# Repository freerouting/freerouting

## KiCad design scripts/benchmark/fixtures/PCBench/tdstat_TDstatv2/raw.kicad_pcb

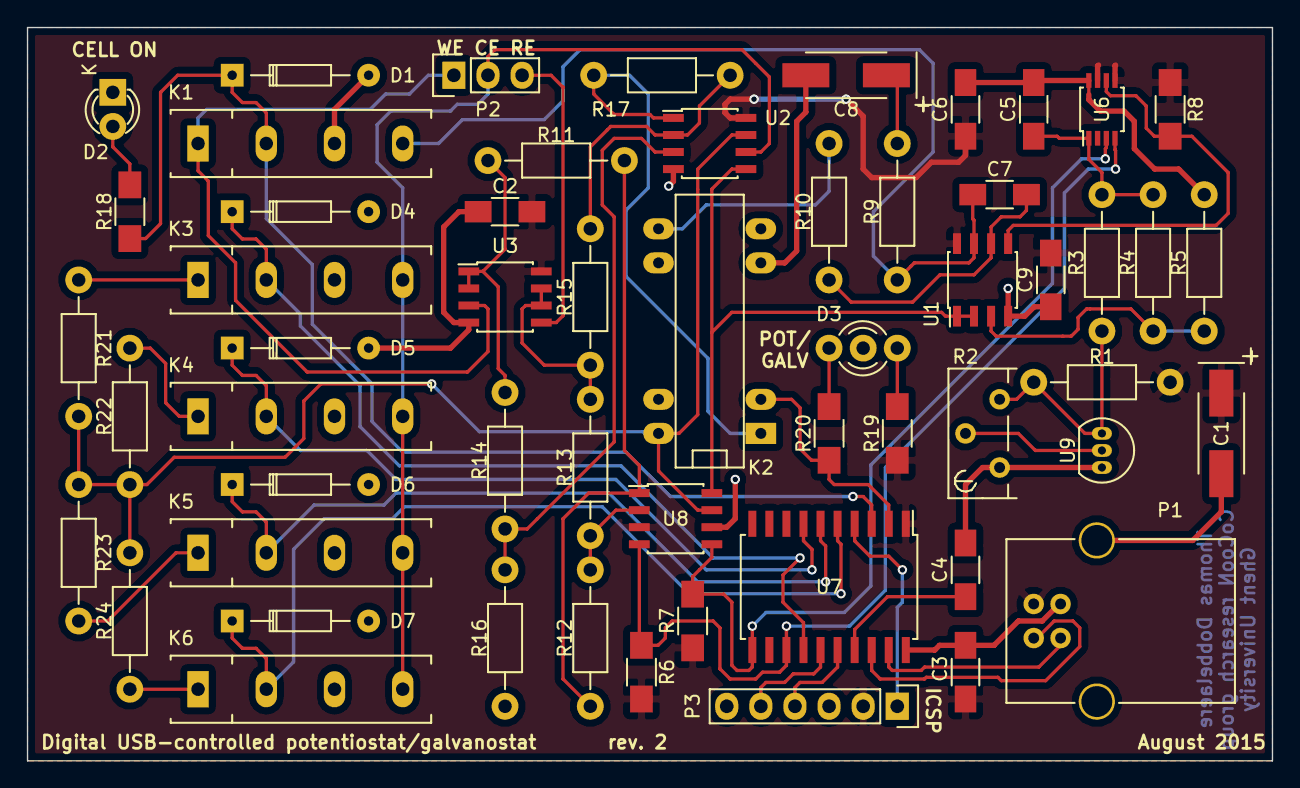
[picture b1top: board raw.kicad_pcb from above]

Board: 2 copper layers, 92.7 x 54.6 mm, 56 parts (0 on the bottom side), 44 nets.

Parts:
C1, C8: 10 µF; TantalC_SizeC_EIA-6032_HandSoldering
C2, C3, C4, C5, C6, C7, C9: 0.1 µF; C_1206_HandSoldering
D1, D4, D5, D6, D7: 1N4148; Diode_DO-35_SOD27_Horizontal_RM10
D2: CELL ON LED; LED-3MM
D3: MODE LED; DUO-LED-3mm
K1, K3, K4, K5, K6: 9007-05-00; RELAY-9007
K2: HE721C0510; RELAY-HE700
P1: USB_B
P2: CELL_CONN; Pin_Header_Straight_1x03
P3: ICSP_CONN; Pin_Header_Straight_1x06
R1: 1k; Resistor_Horizontal_RM10mm
R2: 10k; Potentiometer_Bourns_3296Y_3-8Zoll_Angular_ScrewUp
R3, R23: 10k 0.1%; Resistor_Horizontal_RM10mm
R4: 18k 0.1%; Resistor_Horizontal_RM10mm
R5: 2k 0.1%; Resistor_Horizontal_RM10mm
R6, R7: 4k7; R_1206_HandSoldering
R8: 100k; R_1206_HandSoldering
R9: 27; Resistor_Horizontal_RM10mm
R10: 100k; Resistor_Horizontal_RM10mm
R11, R12, R13, R22: 1k 0.1%; Resistor_Horizontal_RM10mm
R14, R15: 200k 0.1%; Resistor_Horizontal_RM10mm
R16, R17, R24: 100k 0.1%; Resistor_Horizontal_RM10mm
R18, R19, R20: 1k; R_1206_HandSoldering
R21: 100R 0.1%; Resistor_Horizontal_RM10mm
U1, U2, U3: AD8629; SOIC-8_3.9x4.9mm_Pitch1.27mm
U6: MAX5217; TSSOP-8_3x3mm_Pitch0.65mm
U7: PIC16F1459; SOIC-20_7.5x12.8mm_Pitch1.27mm
U8: MCP3422; SOIC-8_3.9x4.9mm_Pitch1.27mm
U9: TL431; TO-92_Inline_Narrow_Oval

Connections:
+5V: C1.1, C2.1, C3.1, C6.1, C9.1, P1.1, P3.2, R1.2, R6.1, R7.1, R8.2, R19.2, U1.8, U2.8, U3.8, U6.5, U6.7, U7.1, U8.3
/CE: K3.4, K4.4, K5.4, K6.4, P2.2, U2.6
/CELL_ON: D1.1, K1.2, R18.2, U7.3
/D+: P1.3, U7.19
/D-: P1.2, U7.18
/GALV_SENSE+: U1.1, U1.2, U2.5, U8.8
/GALV_SENSE-: K2.14, R21.2, R22.2, R23.2, R24.2, U2.7, U8.7
/ICSPCLK: P3.5, U7.15
/ICSPDAT: P3.4, U7.16
/MCLR: P3.1, U7.4
/MODE_SW: K2.2, R20.2, U7.2
/RANGE1: D4.1, K3.2, U7.14
/RANGE2: D5.1, K4.2, U7.7
/RANGE3: D6.1, K5.2, U7.6
/RANGE4: D7.1, K6.2, U7.5
/RE: P2.3, U3.5
/SCL: R7.2, U6.3, U7.11, U8.5
/SDA: R6.2, U6.4, U7.13, U8.4
/V_REF_2.4V: C5.2, R3.2, R4.2, U6.1
/WE: K1.1, P2.1, U3.3
GND: C1.2, C2.2, C3.2, C4.1, C5.1, C6.2, C8.2, C9.2, D1.2, D2.1, D3.2, D4.2, D5.2, D6.2, D7.2, K1.3, K2.6, K3.3, K4.3, K5.3, K6.3, P1.4, P1.5, P3.3, R2.1, R5.1, R16.2, U1.4, U2.4, U3.4, U6.8, U7.20, U8.6, U9.3
unnamed: C4.2, U7.17
unnamed: C7.1, K1.4, R9.1, U1.7
unnamed: C7.2, R10.2, U1.6
unnamed: C8.1, R9.2
unnamed: D2.2, R18.1
unnamed: D3.1, R19.1
unnamed: D3.3, R20.1
unnamed: K2.1, R17.2, U2.1
unnamed: K2.8, R10.1
unnamed: K3.1, R21.1
unnamed: K4.1, R22.1
unnamed: K5.1, R23.1
unnamed: K6.1, R24.1
unnamed: R1.1, R2.3, R3.1, U9.1
unnamed: R2.2, U9.2
unnamed: R4.1, R5.2, U1.3
unnamed: R8.1, U1.5, U6.6
unnamed: R11.1, R12.2, U8.1
unnamed: R11.2, R14.2, U3.1, U3.2
unnamed: R12.1, R13.2, U8.2
unnamed: R13.1, R15.1, U3.6, U3.7
unnamed: R14.1, R16.1, U2.3
unnamed: R15.2, R17.1, U2.2

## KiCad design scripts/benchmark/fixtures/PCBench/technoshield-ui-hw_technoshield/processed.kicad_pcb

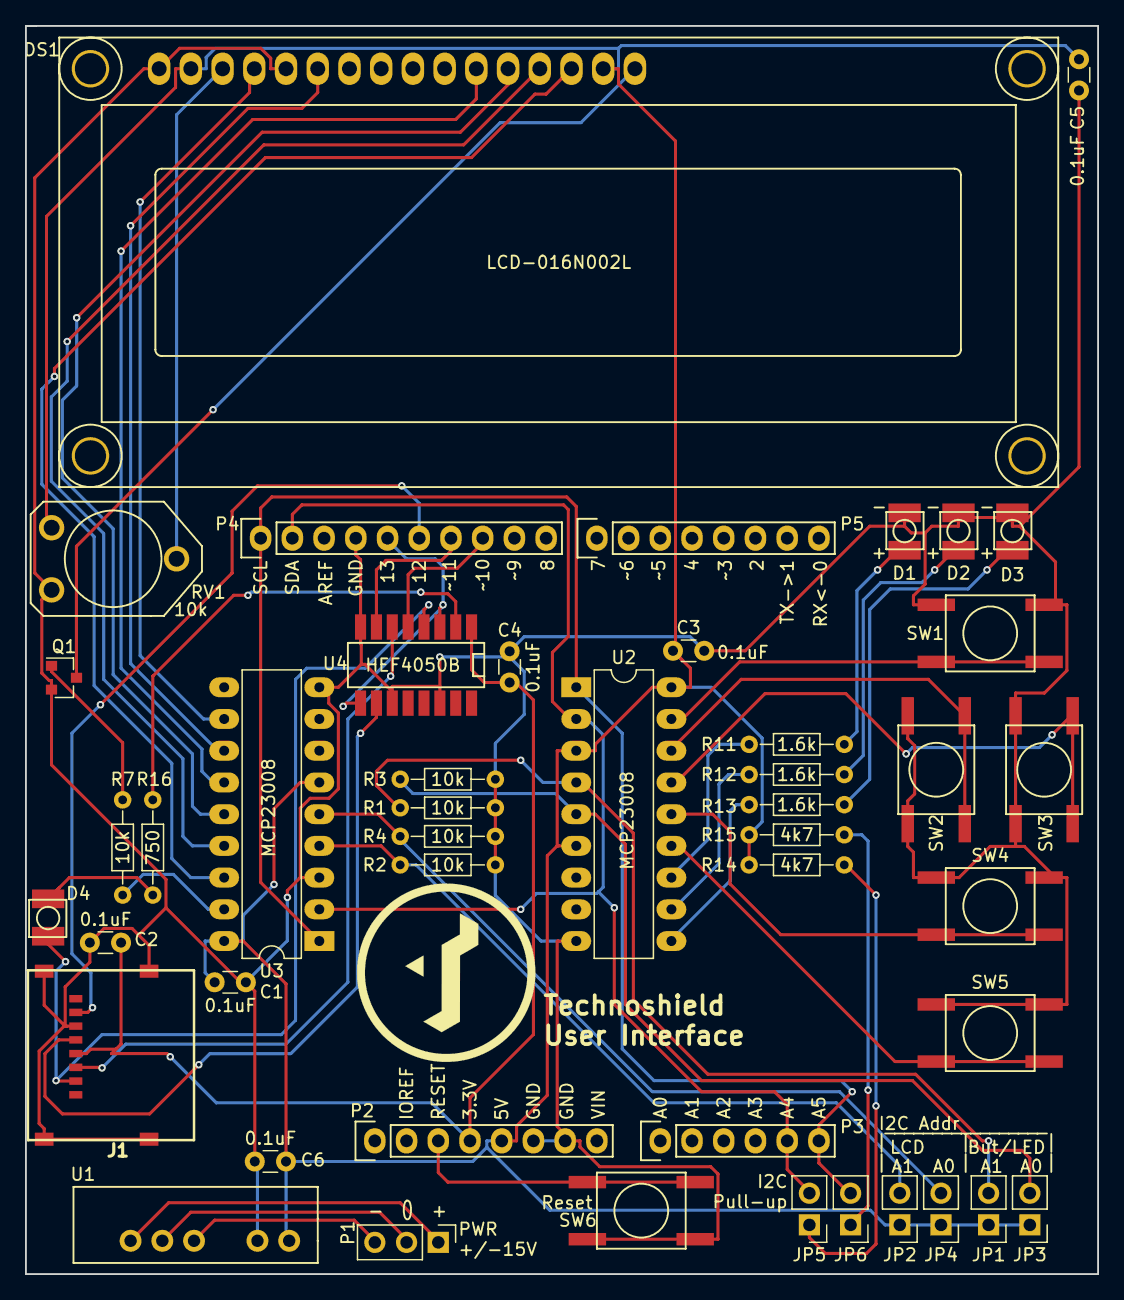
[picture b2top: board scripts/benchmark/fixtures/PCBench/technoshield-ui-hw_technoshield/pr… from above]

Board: 2 copper layers, 85.9 x 99.9 mm, 46 parts (0 on the bottom side), 45 nets.

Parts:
C1, C2, C3, C4, C5, C6: 0.1uF; C_Disc_D3.0mm_W1.6mm_P2.50mm
D1: LS T67K-J1K2-1-Z; T67K
D2: LY T67K-J2L1-26-Z; T67K
D3, D4: LP T67K-E1F2-25-Z; T67K
DS1: LCD-016N002L; WC1602A
J1: 101-00303-68-1-ND; MICRO_SD_HINGE_AMP
JP1, JP2, JP3, JP4, JP5, JP6: JUMPER; Pin_Header_Straight_1x02_Pitch2.54mm
P1: CONN_01X03; Pin_Header_Straight_1x03_Pitch2.54mm
P2: Power; Socket_Strip_Arduino_1x08
P3: Analog; Socket_Strip_Arduino_1x06
P4: Digital; Socket_Strip_Arduino_1x10
P5: Digital; Socket_Strip_Arduino_1x08
Q1: MMBT2222A-7-F; SOT-23
R1, R2, R3, R4, R7: 10k; R_Axial_DIN0204_L3.6mm_D1.6mm_P7.62mm_Horizontal
R11, R12, R13: 1.6k; R_Axial_DIN0204_L3.6mm_D1.6mm_P7.62mm_Horizontal
R14, R15: 4k7; R_Axial_DIN0204_L3.6mm_D1.6mm_P7.62mm_Horizontal
R16: 750; R_Axial_DIN0204_L3.6mm_D1.6mm_P7.62mm_Horizontal
RV1: 10k; POTENTIOMETRE_BOURNS_3319P
SW1, SW2, SW3, SW4, SW5, SW6: SW_PUSH; smt_btn
U1: PDM1-S5-D15-S; PDM1-S
U2, U3: MCP23008; DIP-18_W7.62mm_LongPads
U4: HEF4050B; SO16-3_9mm

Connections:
+3V3: C2.1, C4.1, J1.4, P2.4, U4.1
+5V: C1.1, C3.1, C5.1, C6.1, DS1.2, DS1.15, JP1.1, JP2.1, JP3.1, JP4.1, P2.5, R14.1, R15.1, RV1.1, U1.1, U2.3, U2.6, U2.18, U3.6, U3.18
/10(**/SS): P4.8, U4.5
/11(**/MOSI): P4.7, U4.7
/12(MISO): J1.7, P4.6
/13(SCK): P4.5, U4.3, U4.9
/A4(SDA): JP5.2, P3.5, P4.2, U2.2, U3.2
/A5(SCL): JP6.2, P3.6, P4.1, U2.1, U3.1
/Reset: P2.3, SW6.2
GND: C1.2, C2.2, C3.2, C4.2, C5.2, C6.2, D1.1, D2.1, D3.1, DS1.1, DS1.5, J1.6, J1.SHLD, P2.6, P2.7, P4.4, Q1.2, R1.2, R2.2, R3.2, R4.2, RV1.3, SW1.2, SW2.2, SW3.2, SW4.2, SW5.2, SW6.1, U1.2, U2.9, U3.3, U3.9, U4.8, U4.11, U4.14
unnamed: D1.2, R11.1
unnamed: D2.2, R12.1
unnamed: D3.2, R13.1
unnamed: D4.1, J1.2, U4.4
unnamed: D4.2, R16.1
unnamed: DS1.3, RV1.2
unnamed: DS1.4, U3.11
unnamed: DS1.6, U3.12
unnamed: DS1.11, U3.13
unnamed: DS1.12, U3.14
unnamed: DS1.13, U3.15
unnamed: DS1.14, U3.16
unnamed: DS1.16, Q1.3
unnamed: J1.3, U4.6
unnamed: J1.5, U4.10
unnamed: JP1.2, R1.1, U2.4
unnamed: JP2.2, R2.1, U3.4
unnamed: JP3.2, R3.1, U2.5
unnamed: JP4.2, R4.1, U3.5
unnamed: JP5.1, R14.2
unnamed: JP6.1, R15.2
unnamed: P1.1, U1.6
unnamed: P1.2, U1.5
unnamed: P1.3, U1.4
unnamed: Q1.1, R7.1
unnamed: R7.2, U3.17
unnamed: R11.2, U2.12
unnamed: R12.2, U2.11
unnamed: R13.2, U2.10
unnamed: R16.2, U4.2
unnamed: SW1.1, U2.17
unnamed: SW2.1, U2.16
unnamed: SW3.1, U2.15
unnamed: SW4.1, U2.14
unnamed: SW5.1, U2.13

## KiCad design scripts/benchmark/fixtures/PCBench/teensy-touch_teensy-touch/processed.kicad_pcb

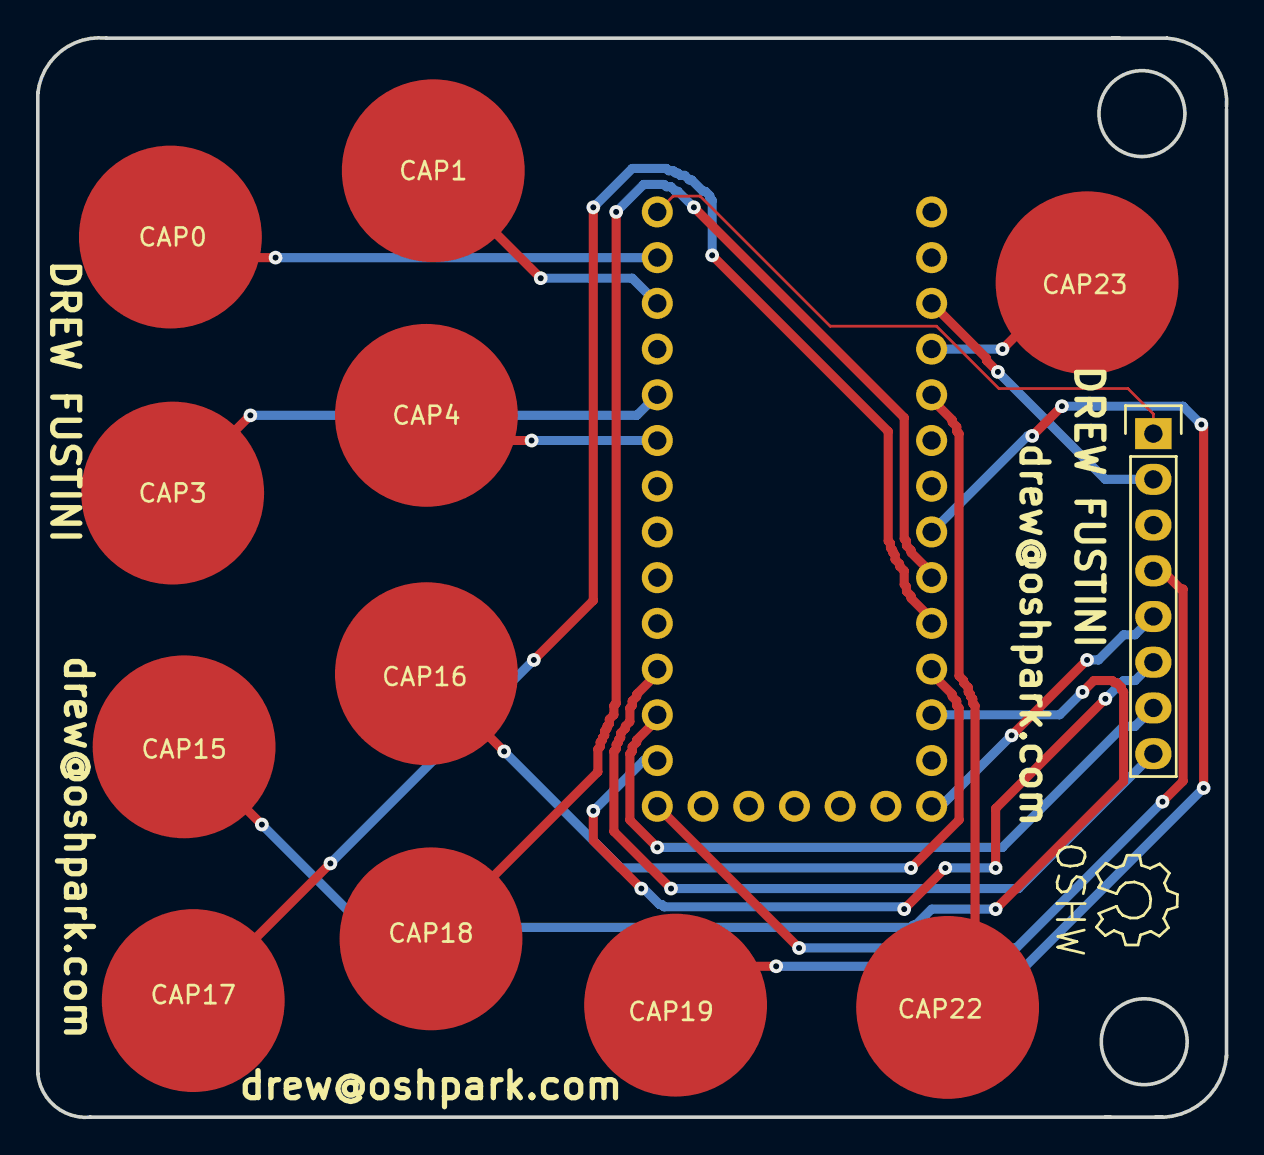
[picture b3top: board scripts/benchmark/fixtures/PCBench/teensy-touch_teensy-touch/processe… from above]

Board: 2 copper layers, 66.0 x 60.0 mm, 13 parts (0 on the bottom side), 18 nets.

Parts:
CAP0, CAP1, CAP3, CAP4, CAP15, CAP16, CAP17, CAP18, CAP19, CAP22, CAP23: CAPSENSE_CIRCLE; CAPSENSE_CIRCLE_D10
J1: TEENSY-LC
J2: OLED_128x64; Pin_Header_Straight_1x08

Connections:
/CAP15: CAP15.1, J1.15
/CAP16: CAP16.1, J1.16
/CAP17: CAP17.1, J1.17
/CAP18: CAP18.1, J1.18
/CAP19: CAP19.1, J1.19
/CAP22: CAP22.1, J1.22
/CAP23: CAP23.1, J1.23
/CLK: J1.10, J2.7
/CS: J1.12, J2.4
/DC: J1.11, J2.6
/Data: J1.9, J2.8
/GND: J1.G1, J2.1
/RST: J1.13, J2.5
/VIN: J1.3V2, J2.2
unnamed: CAP0.1, J1.0
unnamed: CAP1.1, J1.1
unnamed: CAP3.1, J1.3
unnamed: CAP4.1, J1.4

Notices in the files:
scripts/benchmark/fixtures/PCBench/technoshield-ui-hw_technoshield/processed.kicad_pcb:
Released under the Creative Commons Attribution Share-Alike 4.0 License
Copyright 2017 Jean-Sébastien Castonguay
